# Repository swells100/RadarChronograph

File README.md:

# Radar Chronograph

This repository holds the code for the Radar Chronograph and links to the board and manual repositories.

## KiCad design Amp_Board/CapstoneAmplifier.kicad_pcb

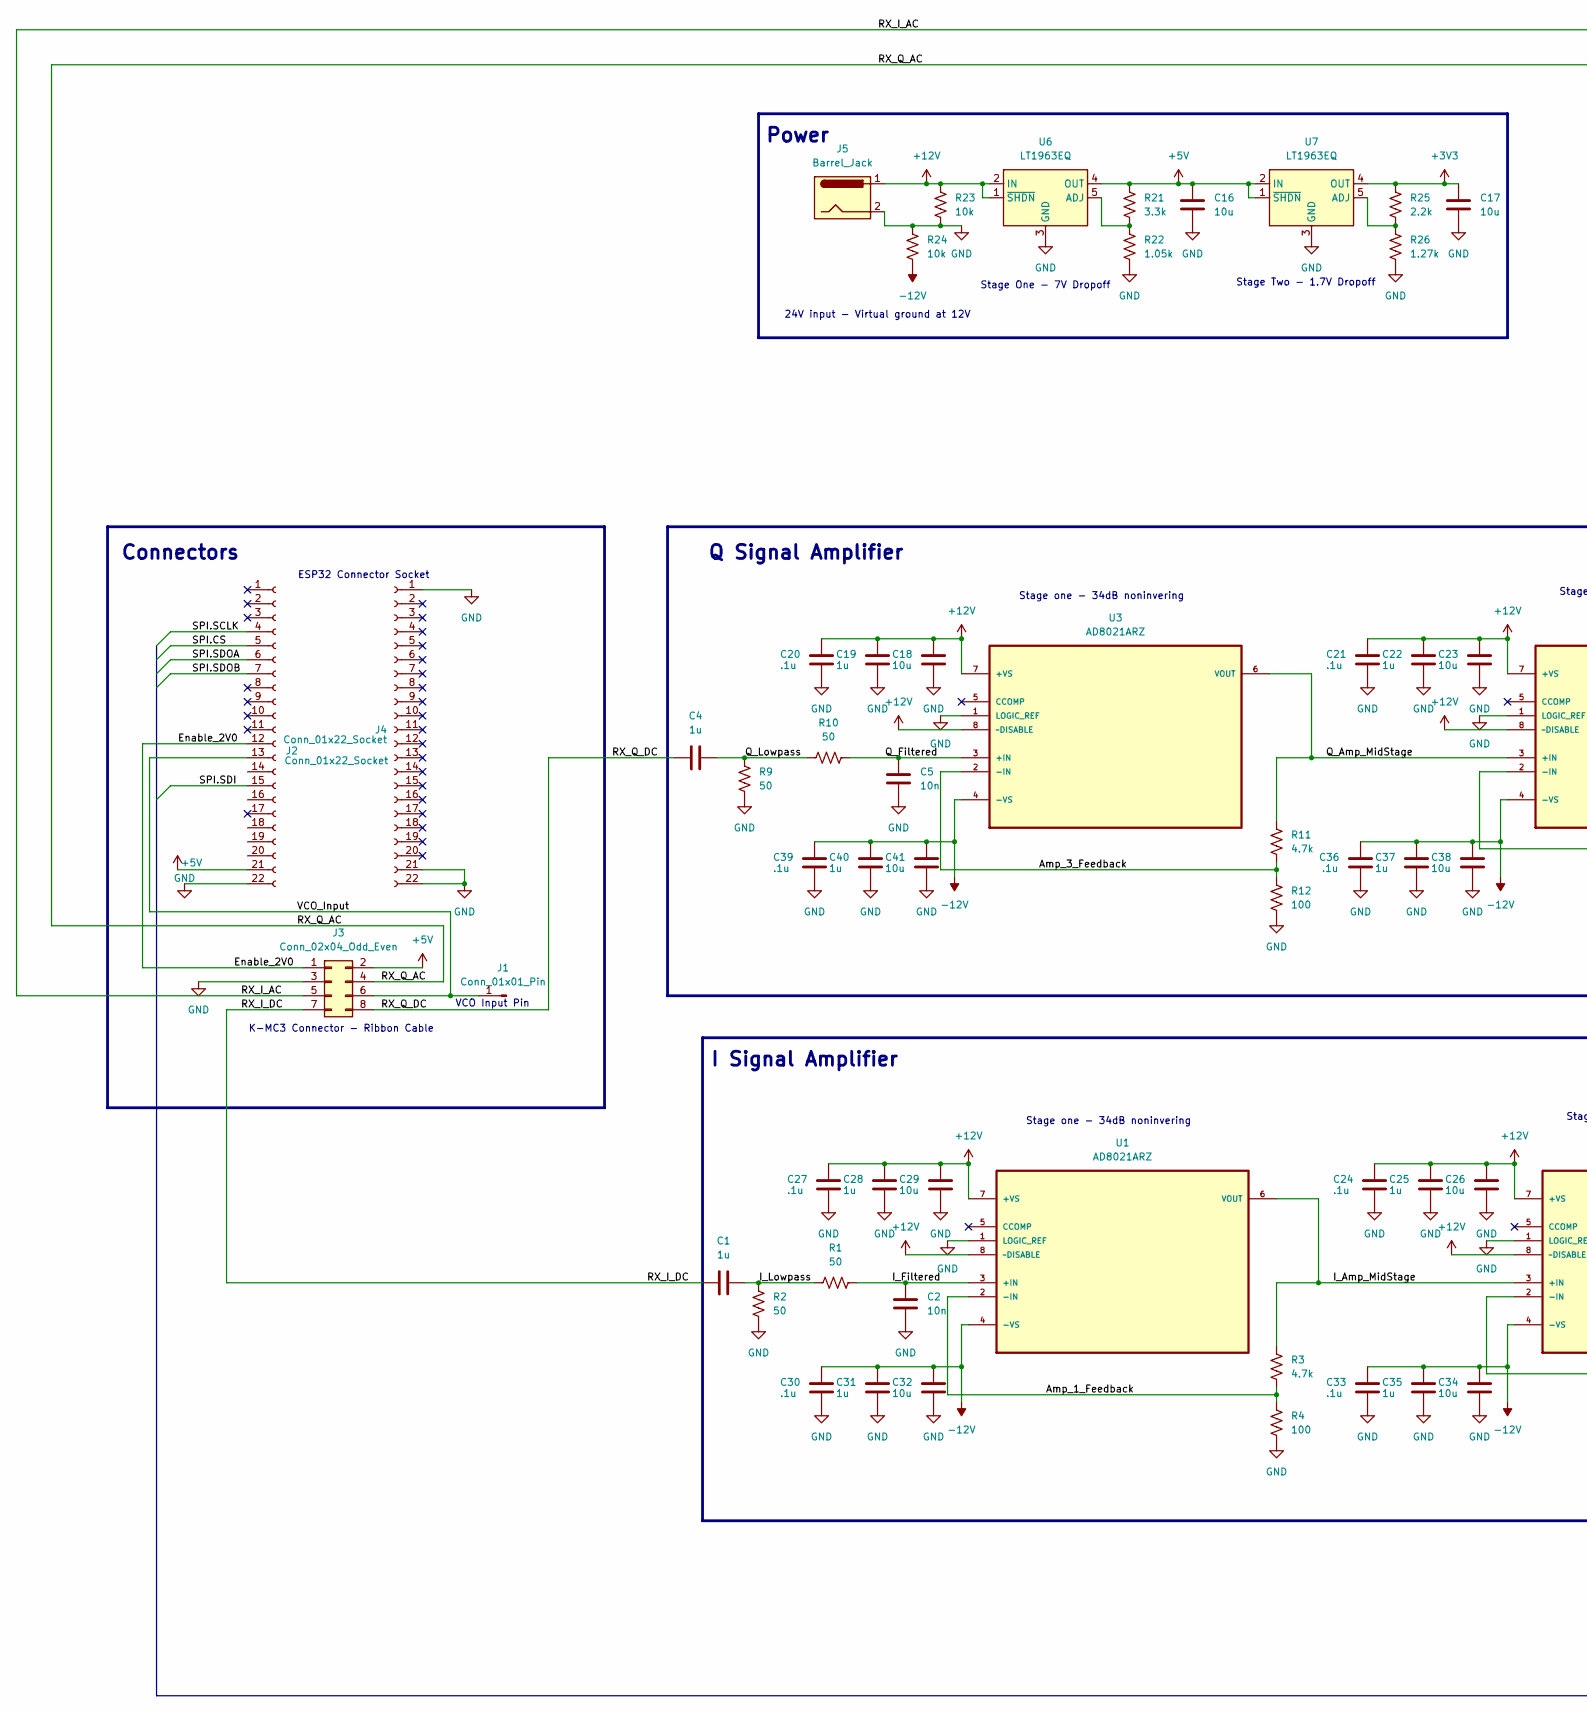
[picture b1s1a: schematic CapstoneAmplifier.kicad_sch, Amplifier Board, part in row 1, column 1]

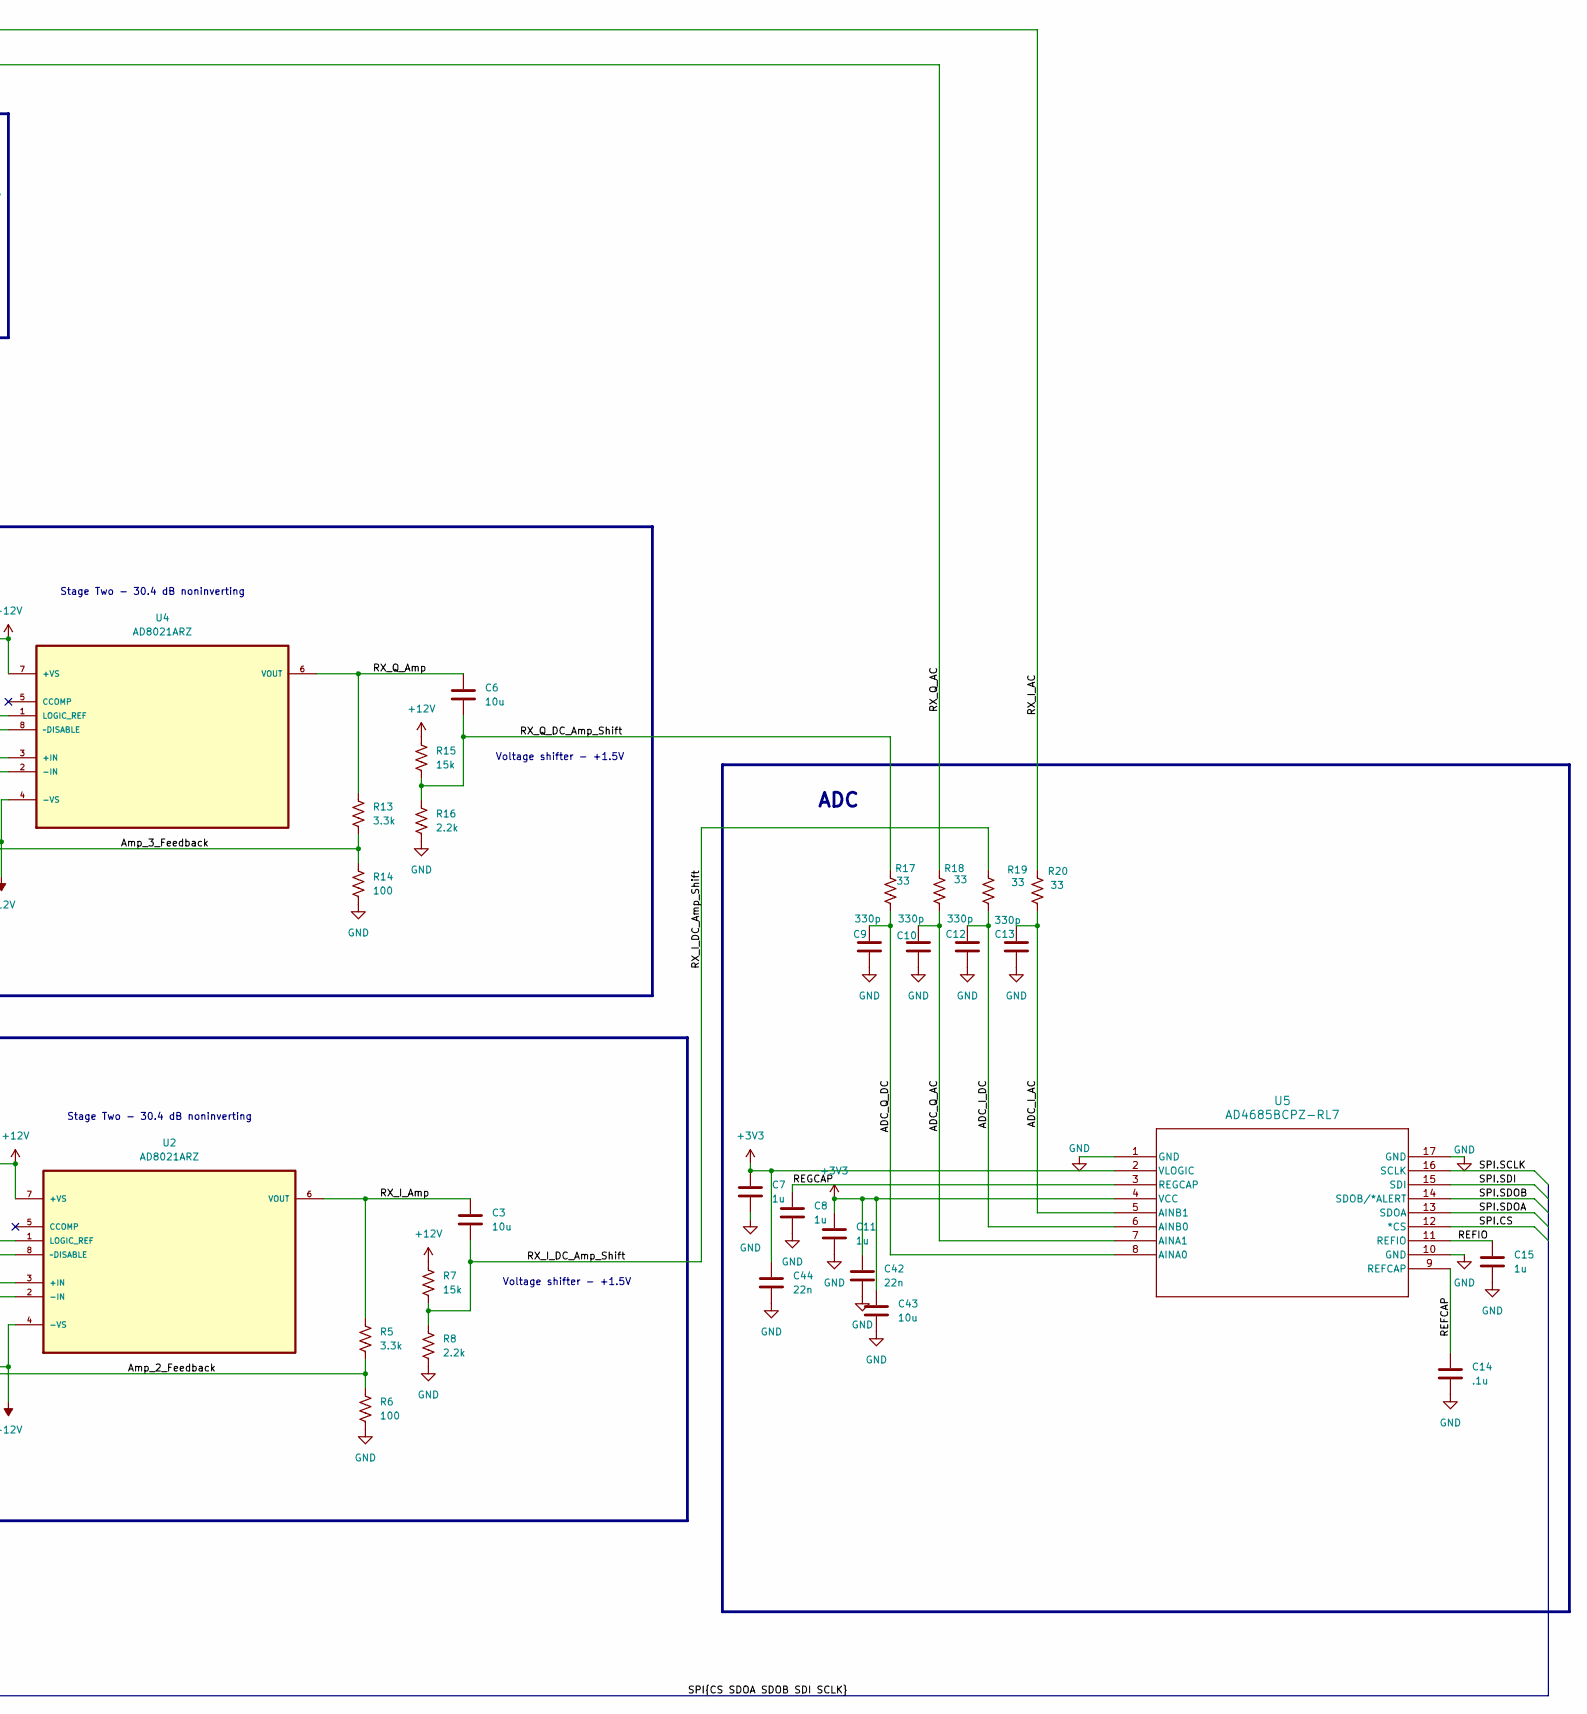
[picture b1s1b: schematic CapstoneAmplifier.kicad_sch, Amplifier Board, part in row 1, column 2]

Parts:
C1, C4, C7, C8, C11, C15, C25: 1u; C_0603_1608Metric_Pad1.08x0.95mm_HandSolder
C2, C5: 10n; C_0603_1608Metric_Pad1.08x0.95mm_HandSolder
C3, C6, C26, C43: 10u; C_0603_1608Metric_Pad1.08x0.95mm_HandSolder
C9, C10, C12, C13: 330p; C_0603_1608Metric_Pad1.08x0.95mm_HandSolder
C14, C24: .1u; C_0603_1608Metric_Pad1.08x0.95mm_HandSolder
C16, C17, C18, C23, C29, C32, C34, C38, C41: 10u; C_0603_1608Metric
C19, C22, C28, C31, C35, C37, C40: 1u; C_0603_1608Metric
C20, C21, C27, C30, C33, C36, C39: .1u; C_0603_1608Metric
C42, C44: 22n; C_0603_1608Metric_Pad1.08x0.95mm_HandSolder
J1: Conn_01x01_Pin; PinHeader_1x01_P1.00mm_Vertical
J2, J4: Conn_01x22_Socket; PinHeader_1x22_P2.00mm_Vertical
J3: Conn_02x04_Odd_Even; PinHeader_2x04_P2.54mm_Vertical
J5: Barrel_Jack; BarrelJack_CUI_PJ-063AH_Horizontal
R1, R2, R9, R10: 50; R_0603_1608Metric_Pad0.98x0.95mm_HandSolder
R3, R11: 4.7k; R_0603_1608Metric_Pad0.98x0.95mm_HandSolder
R4, R6, R12, R14: 100; R_0603_1608Metric_Pad0.98x0.95mm_HandSolder
R5, R13, R21: 3.3k; R_0603_1608Metric_Pad0.98x0.95mm_HandSolder
R7, R15: 15k; R_0603_1608Metric_Pad0.98x0.95mm_HandSolder
R8, R16, R25: 2.2k; R_0603_1608Metric_Pad0.98x0.95mm_HandSolder
R17, R18, R19, R20: 33; R_0603_1608Metric_Pad0.98x0.95mm_HandSolder
R22: 1.05k; R_0603_1608Metric_Pad0.98x0.95mm_HandSolder
R23, R24: 10k; R_0603_1608Metric_Pad0.98x0.95mm_HandSolder
R26: 1.27k; R_0603_1608Metric_Pad0.98x0.95mm_HandSolder
U1, U2, U3, U4: AD8021ARZ; AD8021; MPN AD8021ARZ
U5: AD4685BCPZ-RL7; CP-16-45_ADI
U6, U7: LT1963EQ; TO-263-5_TabPin3

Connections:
+3V3: C7.2, C11.2, C17.1, C42.2, C43.2, C44.2, R25.1, U5.2 (VLOGIC), U5.4 (VCC), U7.4 (OUT)
+5V: C16.1, J2.21, J3.2, R21.1, U6.4 (OUT), U7.1 (~SHDN), U7.2 (IN)
+12V: C18.1, C19.1, C20.1, C21.1, C22.1, C23.1, C24.1, C25.1, C26.1, C27.1, C28.1, C29.1, J5.1, R7.1, R15.1, R23.1, U1.7 (+VS), U1.8 (~DISABLE), U2.7 (+VS), U2.8 (~DISABLE), U3.7 (+VS), U3.8 (~DISABLE), U4.7 (+VS), U4.8 (~DISABLE), U6.1 (~SHDN), U6.2 (IN)
-12V: C30.1, C31.1, C32.1, C33.1, C34.1, C35.1, C36.1, C37.1, C38.1, C39.1, C40.1, C41.1, R24.2, U1.4 (-VS), U2.4 (-VS), U3.4 (-VS), U4.4 (-VS)
/<NO NET>: J1.1, J2.13, J3.6
/ADC_I_AC: C13.2, R20.2, U5.5 (AINB1)
/ADC_I_DC: C12.2, R19.2, U5.6 (AINB0)
/ADC_Q_AC: C10.2, R18.2, U5.7 (AINA1)
/ADC_Q_DC: C9.2, R17.2, U5.8 (AINA0)
/Amp_1_Feedback: R3.2, R4.1, U1.2 (-IN)
/Amp_2_Feedback: R5.2, R6.1, U2.2 (-IN)
/Amp_3_Feedback: R11.2, R12.1, R13.2, R14.1, U3.2 (-IN), U4.2 (-IN)
/Enable_2V0: J2.12, J3.1
/I_Amp_MidStage: R3.1, U1.6 (VOUT), U2.3 (+IN)
/I_Filtered: C2.1, R1.2, U1.3 (+IN)
/I_Lowpass: C1.2, R1.1, R2.1
/Q_Amp_MidStage: R11.1, U3.6 (VOUT), U4.3 (+IN)
/Q_Filtered: C5.1, R10.2, U3.3 (+IN)
/Q_Lowpass: C4.2, R9.1, R10.1
/REFCAP: C14.2, U5.9 (REFCAP)
/REFIO: C15.2, U5.11 (REFIO)
/REGCAP: C8.2, U5.3 (REGCAP)
/RX_I_AC: J3.5, R20.1
/RX_I_Amp: C3.1, R5.1, U2.6 (VOUT)
/RX_I_DC: C1.1, J3.7
/RX_I_DC_Amp_Shift: C3.2, R7.2, R8.1, R19.1
/RX_Q_AC: J3.4, R18.1
/RX_Q_Amp: C6.1, R13.1, U4.6 (VOUT)
/RX_Q_DC: C4.1, J3.8
/RX_Q_DC_Amp_Shift: C6.2, R15.2, R16.1, R17.1
/SPI.CS: J2.5, U5.12 (*CS)
/SPI.SCLK: J2.4, U5.16 (SCLK)
/SPI.SDI: J2.15, U5.15 (SDI)
/SPI.SDOA: J2.6, U5.13 (SDOA)
/SPI.SDOB: J2.7, U5.14 (SDOB/*ALERT)
GND: C2.2, C5.2, C7.1, C8.1, C9.1, C10.1, C11.1, C12.1, C13.1, C14.1, C15.1, C16.2, C17.2, C18.2, C19.2, C20.2, C21.2, C22.2, C23.2, C24.2, C25.2, C26.2, C27.2, C28.2, C29.2, C30.2, C31.2, C32.2, C33.2, C34.2, C35.2, C36.2, C37.2, C38.2, C39.2, C40.2, C41.2, C42.1, C43.1, C44.1, J2.22, J3.3, J4.1, J4.21, J4.22, J5.2, R2.2, R4.2, R6.2, R8.2, R9.2, R12.2, R14.2, R16.2, R22.2, R23.2, R24.1, R26.2, U1.1 (LOGIC_REF), U2.1 (LOGIC_REF), U3.1 (LOGIC_REF), U4.1 (LOGIC_REF), U5.1 (GND), U5.10 (GND), U5.17 (GND), U6.3 (GND), U7.3 (GND)
unnamed: R21.2, R22.1, U6.5 (ADJ)
unnamed: R25.2, R26.1, U7.5 (ADJ)

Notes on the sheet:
Voltage shifter - +1.5V
ESP32 Connector Socket
I Signal Amplifier
Q Signal Amplifier
24V input - Virtual ground at 12V
Power
Connectors
Stage Two - 30.4 dB noninverting
Stage one - 34dB noninvering
VCO Input Pin
Stage Two - 1.7V Dropoff
K-MC3 Connector - Ribbon Cable
Stage One - 7V Dropoff
ADC

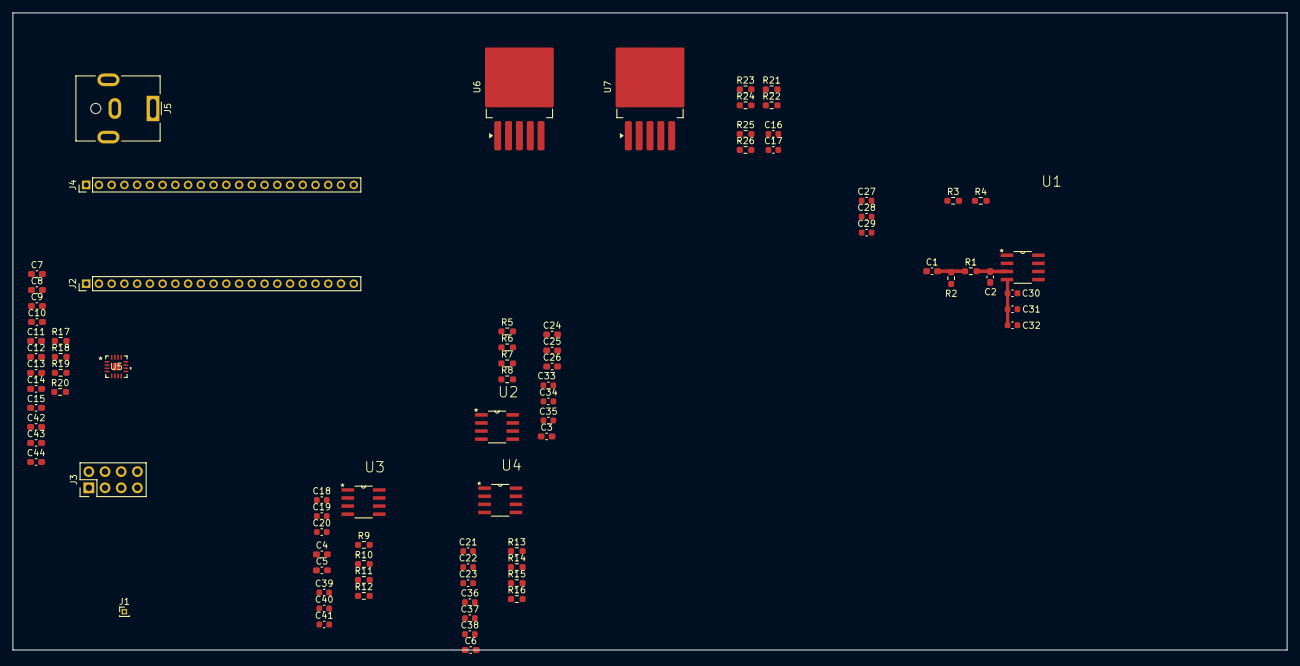
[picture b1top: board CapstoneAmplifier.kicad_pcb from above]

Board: 2 copper layers, 200.0 x 100.0 mm, 82 parts (0 on the bottom side), 38 nets.
